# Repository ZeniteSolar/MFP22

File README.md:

# MFP19
**M**ódulo da **F**onte **P**rincipal 2019  
Embarcação Guarapuvu II  
Equipe Zênite Solar  

### Sobre

Este módulo é responsável por fornecer uma tensao fixa e estavel de 18V para alimentaçao dos modulos que estao na rede CAN

### Images

#### Requisitos e Abordagens
1. Fornecer tensao estavel de 18V 
    - Manter a tensao estavel independente da carga (até 3A)
    - Baixo ripple
2. Ser robusta
    - Nao queimar por curto-circuito
    - Nao queimar por sobre temperatura
    - Nao queimar por sobre-carga
    - Resistencia por ruido eletromagnetico e eletrico causados pelos componentes do sistema (motor,MCC...)
3. Eficiencia energetica.
    -Conversor estatico DC/DC chaveado
4. Facilitar o diagnóstico
    - Utilizar LEDs
    
**CI Ultilizado: Conversor LMR16030**
[Datasheet](https://www.ti.com/lit/ds/symlink/lmr16030.pdf?ts=1596324314390&ref_url=https%253A%252F%252Fwww.google.com%252F)

#### Projeto do Indutor

   -seleção do indutor de saida:

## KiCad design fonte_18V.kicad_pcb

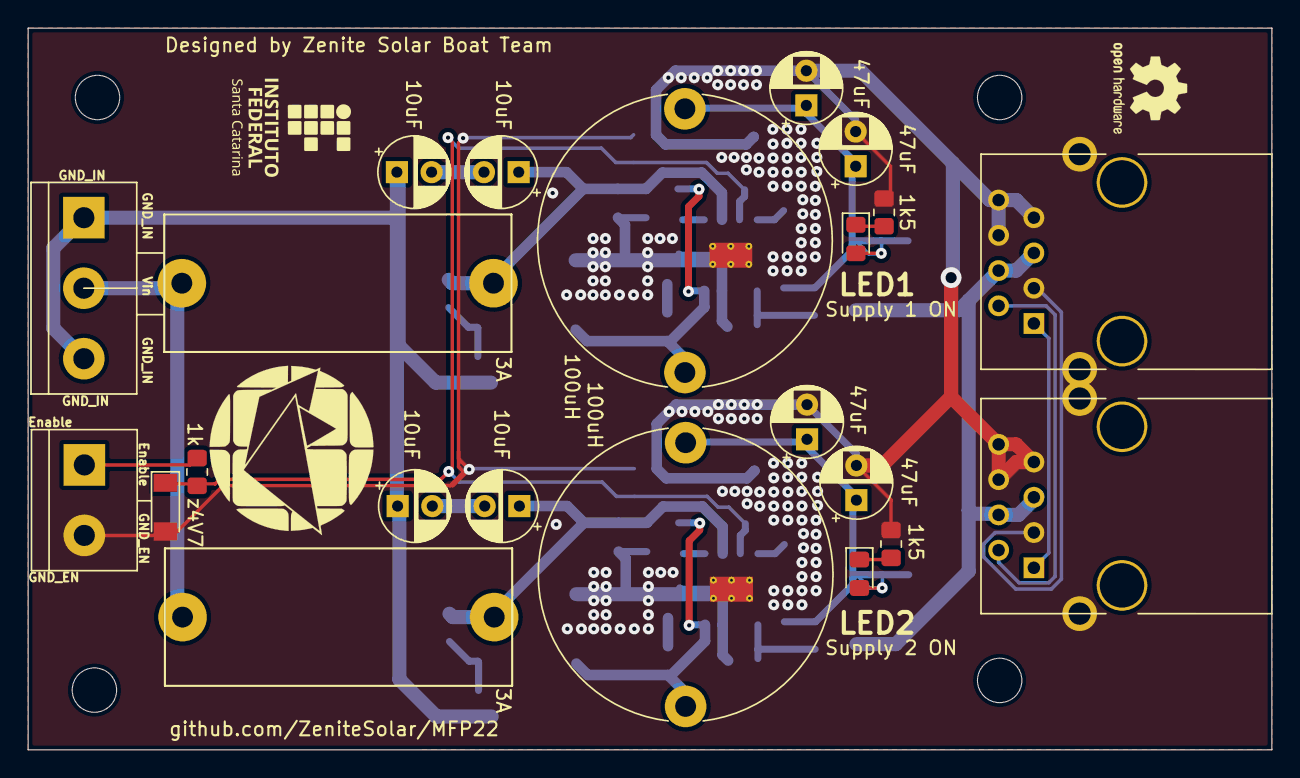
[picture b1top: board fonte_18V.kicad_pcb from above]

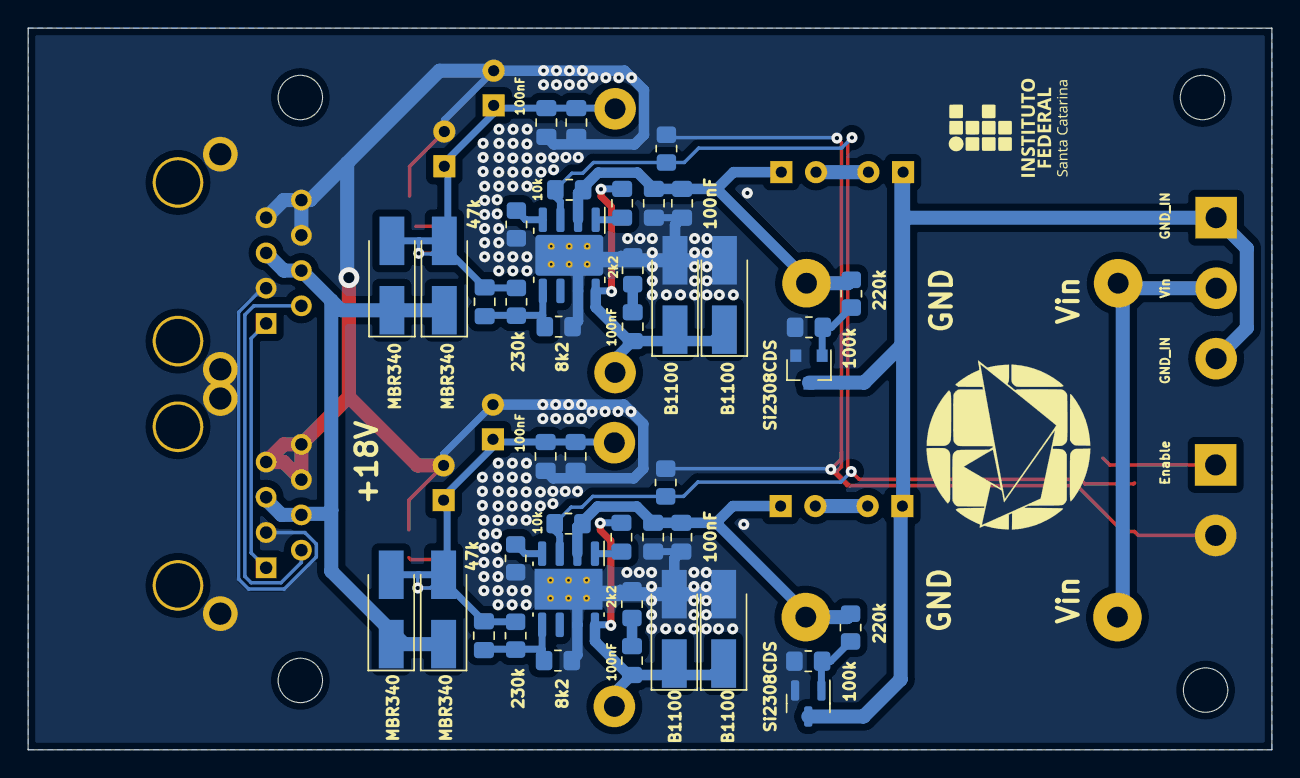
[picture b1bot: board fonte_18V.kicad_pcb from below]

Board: 2 copper layers, 89.6 x 52.0 mm, 73 parts (44 on the bottom side), 28 nets.

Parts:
CBoot1, CBoot301: 100nF; C_0805_2012Metric_Pad1.18x1.45mm_HandSolder
Cff1, Cff301: na; C_0805_2012Metric_Pad1.18x1.45mm_HandSolder
Ci1, Ci301: 10u; CP_Radial_D5.0mm_P2.50mm
Cie101, Cie301: 10u; CP_Radial_D5.0mm_P2.50mm
Cin2, Cin3, Cin301, Cin302: 100nF; C_0805_2012Metric_Pad1.18x1.45mm_HandSolder
Co1, Co2, Co301, Co302: 47u; CP_Radial_D5.0mm_P2.50mm
Co3, Co303: o.1u; C_0805_2012Metric_Pad1.18x1.45mm_HandSolder
Co4, Co304: 0.1u; C_0805_2012Metric_Pad1.18x1.45mm_HandSolder
Cs1, Cs301: 100n; C_0805_2012Metric_Pad1.18x1.45mm_HandSolder
D101: 4v7; D_MiniMELF
D102, D201, D303, D304: MBR340; D_SMA_Handsoldering
D103, D104, D301, D302: B1100; D_SMA_Handsoldering
F101, F301: Fuse; Fuse_Holder_5x20
H1, H2, H3, H4: MountingHole; MountingHole_3.2mm_M3
J101: IN; TerminalBlock_bornier-3_P5.08mm
J102: Conn_01x02; TerminalBlock_bornier-2_P5.08mm
J401, J402: RJ45_Shielded; RJ45_YH59_01
L1, L301: 100uH; L_Radial_D21.0mm_P19.00mm
LOGO101: Logo_Open_Hardware_Small; OSHW-Logo2_7.3x6mm_SilkScreen
Led1, Led101: LED; LED_0805_2012Metric_Pad1.15x1.40mm_HandSolder
Q1, Q301: Si2308CDS; SOT-23
R1, R305: 47k; R_0805_2012Metric_Pad1.20x1.40mm_HandSolder
R2: 1k; R_0805_2012Metric_Pad1.20x1.40mm_HandSolder
R3, R301: 220K; R_0805_2012Metric_Pad1.20x1.40mm_HandSolder
R4, R302: 100K; R_0805_2012Metric_Pad1.20x1.40mm_HandSolder
R5, R303: 10K; R_0805_2012Metric_Pad1.20x1.40mm_HandSolder
R6, R304: NA; R_0805_2012Metric_Pad1.20x1.40mm_HandSolder
RLed1, RLed101: 1k5; R_0805_2012Metric_Pad1.20x1.40mm_HandSolder
Rfbb1, Rfbb301: 8k2; R_0805_2012Metric_Pad1.20x1.40mm_HandSolder
Rfbt2, Rfbt301: 230k; R_0805_2012Metric_Pad1.20x1.40mm_HandSolder
Rs1, Rs301: 2k2; R_0805_2012Metric_Pad1.20x1.40mm_HandSolder
SYM101, SYM102: SYM_Flash_Small; symbol_logoZenite
SYM103, SYM104: SYM_Flash_Small; synbol_logoifsc
U1, U301: LMR16030; Texas_R-PDSO-G8_EP2.95x4.9mm_Mask2.4x3.1mm_ThermalVias

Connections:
/CAN/CAN_18V: D102.1 (K), D201.1 (K), D303.1 (K), D304.1 (K), J401.4, J401.5, J402.4, J402.5
/EN: D101.1 (K), R2.1, R5.1, R6.2, R303.1, R304.2, U1.3 (EN), U301.3 (EN)
/supply1/CAN_18V_DIODE: Cff1.1, Co1.1, Co2.1, Co3.1, Co4.1, D102.2 (A), D201.2 (A), L1.2, Led1.2 (A), Rfbt2.1
/supply1/Feedback: Cff1.2, Rfbb1.1, Rfbt2.2, U1.5 (FB)
/supply1/GND_IN: Cie101.1, Cie301.1, J101.1, J101.3, Q1.3 (D), Q301.3 (D)
/supply1/IN: F101.1, F301.1, J101.2
/supply1/snbr: Cs1.2, Rs1.1
/supply2/CAN_18V_DIODE: Cff301.1, Co301.1, Co302.1, Co303.1, Co304.1, D303.2 (A), D304.2 (A), L301.2, Led101.2 (A), Rfbt301.1
/supply2/Feedback: Cff301.2, Rfbb301.1, Rfbt301.2, U301.5 (FB)
/supply2/snbr: Cs301.2, Rs301.1
GND: Cin2.2, Cin3.2, Cin301.2, Cin302.2, Co1.2, Co2.2, Co3.2, Co4.2, Co301.2, Co302.2, Co303.2, Co304.2, D101.2 (A), D103.2 (A), D104.2 (A), D301.2 (A), D302.2 (A), J102.2, J401.3, J401.6, J401.7, J401.8, J401.SH, J402.3, J402.6, J402.7, J402.8, J402.SH, Q1.2 (S), Q301.2 (S), R1.2, R4.2, R6.1, R302.2, R304.1, R305.2, RLed1.2, RLed101.2, Rfbb1.2, Rfbb301.2, Rs1.2, Rs301.2, U1.7 (GND), U1.9 (Thermal_Pad), U301.7 (GND), U301.9 (Thermal_Pad)
unnamed: CBoot1.1, Cs1.1, D103.1 (K), D104.1 (K), L1.1, U1.8 (SW)
unnamed: CBoot1.2, U1.1 (BOOT)
unnamed: CBoot301.1, Cs301.1, D301.1 (K), D302.1 (K), L301.1, U301.8 (SW)
unnamed: CBoot301.2, U301.1 (BOOT)
unnamed: Ci1.1, Cin2.1, Cin3.1, F101.2, R3.1, R5.2, U1.2 (VIN)
unnamed: Ci1.2, Cie101.2
unnamed: Ci301.1, Cin301.1, Cin302.1, F301.2, R301.1, R303.2, U301.2 (VIN)
unnamed: Ci301.2, Cie301.2
unnamed: J102.1, R2.2
unnamed: J401.1, J402.1
unnamed: J401.2, J402.2
unnamed: Led1.1 (K), RLed1.1
unnamed: Led101.1 (K), RLed101.1
unnamed: Q1.1 (G), R3.2, R4.1
unnamed: Q301.1 (G), R301.2, R302.1
unnamed: R1.1, U1.4 (RT/SYNC)
unnamed: R305.1, U301.4 (RT/SYNC)

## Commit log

2022-06-27 copy MFP19
2022-06-27 Organize schematics for better visualization
2022-06-27 temp
2022-06-29 Duplicate fonts for redundancy and initialized layout
2022-06-29 almost finished
2022-06-29 run DRC and turn invisible reference designators
2022-06-29 Add silkscreen for connectors and author label
2022-06-29 remove backup
2022-06-29 Adjusted silkscreen and fixed RDC errors
2022-06-29 removed duplicated case-insensitive file
2022-06-29 resize board
2022-06-30 Silkscreen updated with JLC. Finished.
2023-02-16 organize repository
2023-02-16 add images
2023-02-16 Organize repo, and update README
